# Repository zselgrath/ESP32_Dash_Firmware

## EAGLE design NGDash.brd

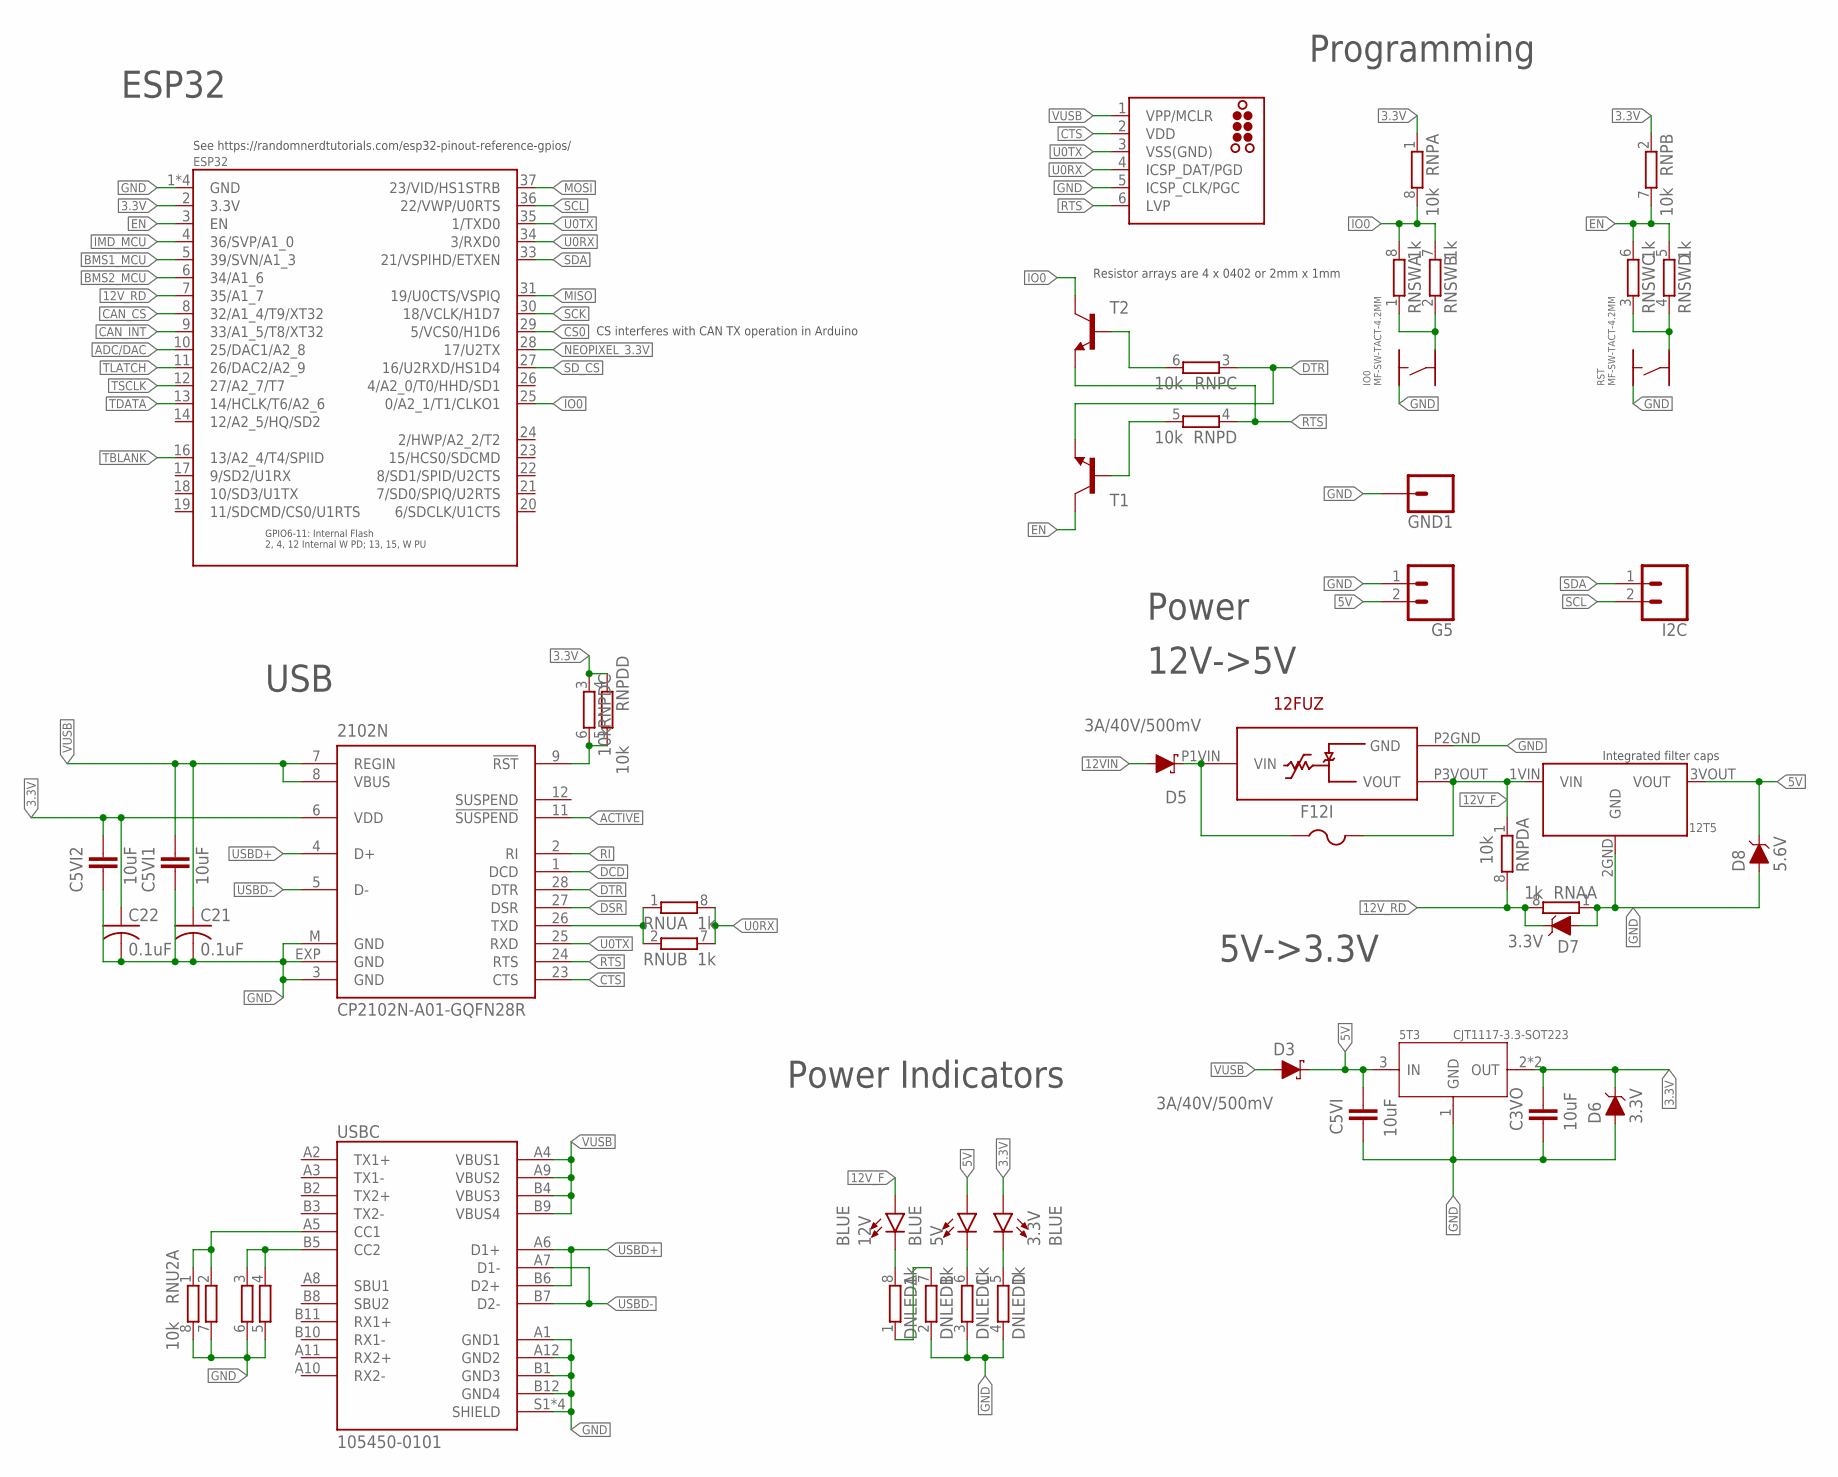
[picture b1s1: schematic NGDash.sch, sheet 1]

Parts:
3.3V, 5V, 12V: BLUE; LED-0603
5T3: CJT1117-3.3-SOT223; SOT-223
12FUZ: LITTELFUSE-POLYZEN-ZEN164V130A24LS
12T5: TRACO-TSR-2-2450
2102N: CP2102N-A01-GQFN28R; MLP28
C3VO, C5VI, C5VI1, C5VI2: 10uF; 1210
C21, C22: 0.1uF; C0603
D3, D5: 3A/40V/500mV; SMA-DIODE
D6, D7: 3.3V; SOD-323
D8: 5.6V; SOD-323
DNLED: 1k; 4X0402ARV341
ESP32: ESP32-WROOM-32; ESP32-WROOM32
F12I: PTCFUSE-1812; 1812
G5: CONN_02; 1X02
GND1: CONN_01; 1X01
I2C: CONN_02; 1X02
IO0: MF-SW-TACT-4.2MM; TACT4.2MM
J2: TC2030-MCP
RNA: 1k; 4X0402ARV341
RNP: 10k; 4X0402ARV341
RNPD: 10k; 4X0402ARV341
RNSW: 1k; 4X0402ARV341
RNU: 1k; 4X0402ARV341
RNU2: 10k; 4X0402ARV341
RST: MF-SW-TACT-4.2MM; TACT4.2MM
T1, T2: BC850-NPN-SOT23-BEC; SOT23-BEC
USBC: 105450-0101; MOLEX_105450-0101

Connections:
3.3V: 3.3V.A, 5T3.2 (OUT), 5T3.TER (OUT), 2102N.6 (VDD), C3VO.1, C5VI2.1, C22.1, D6.C, ESP32.2 (3.3V), RNP.1, RNP.2 (1), RNPD.3 (1), RNPD.4 (1); also elsewhere on the board
5V: 5T3.3 (IN), 5V.A, 12T5.3VOUT (VOUT), C5VI.1, D3.C, D8.C, G5.2; also elsewhere on the board
12VIN: D5.A; also elsewhere on the board
12VRECT: 12FUZ.P1VIN (VIN), D5.C, F12I.1
12V_F: 12FUZ.P3VOUT (VOUT), 12T5.1VIN (VIN), 12V.A, F12I.2, RNPD.1; also elsewhere on the board
12V_RD: D7.C, ESP32.7 (35/A1_7), RNA.8 (2), RNPD.8 (2)
ACTIVE: 2102N.11 (!SUSPEND)
ADC/DAC: ESP32.10 (25/DAC1/A2_8); also elsewhere on the board
BMS1_MCU: ESP32.5 (39/SVN/A1_3); also elsewhere on the board
BMS2_MCU: ESP32.6 (34/A1_6); also elsewhere on the board
CAN_CS: ESP32.8 (32/A1_4/T9/XT32); also elsewhere on the board
CAN_INT: ESP32.9 (33/A1_5/T8/XT32); also elsewhere on the board
CS0: ESP32.29 (5/VCS0/H1D6)
CTS: 2102N.23 (CTS), J2.2 (VDD)
DCD: 2102N.1 (DCD)
DSR: 2102N.27 (DSR)
DTR: 2102N.28 (DTR), RNP.3 (1), T1.E
EN: ESP32.3 (EN), RNP.7 (2), RNSW.5 (2), RNSW.6 (2), T1.C
GND: 5T3.1 (GND), 12FUZ.P2GND (GND), 12T5.2GND (GND), 2102N.3 (GND), 2102N.EXP (GND), 2102N.M (GND), C3VO.2, C5VI.2, C5VI1.2, C5VI2.2, C21.2, C22.2, D6.A, D7.A, D8.A, DNLED.2 (1), DNLED.3 (1), DNLED.4 (1), ESP32.1 (GND), ESP32.15 (GND), ESP32.38 (GND), ESP32.GND, G5.1, GND1.1, IO0.P$1, J2.5 (ICSP_CLK/PGC), RNA.1, RNU2.5 (2), RNU2.6 (2), RNU2.7 (2), RNU2.8 (2), RST.P$1, USBC.A1 (GND1), USBC.A12 (GND2), USBC.B1 (GND3), USBC.B12 (GND4), USBC.S1 (SHIELD), USBC.S2 (SHIELD), USBC.S3 (SHIELD), USBC.S4 (SHIELD); also elsewhere on the board
IMD_MCU: ESP32.4 (36/SVP/A1_0); also elsewhere on the board
IO0: ESP32.25 (0/A2_1/T1/CLKO1), RNP.8 (2), RNSW.7 (2), RNSW.8 (2), T2.C
MISO: ESP32.31 (19/U0CTS/VSPIQ); also elsewhere on the board
MOSI: ESP32.37 (23/VID/HS1STRB); also elsewhere on the board
unnamed: 5V.C, DNLED.6 (2)
unnamed: IO0.P$4, RNSW.1, RNSW.2 (1)
unnamed: RNP.5 (2), T1.B
unnamed: RNP.6 (2), T2.B
unnamed: RNU2.1, RNU2.2 (1), USBC.A5 (CC1)
unnamed: RNSW.3 (1), RNSW.4 (1), RST.P$4
unnamed: 3.3V.C, DNLED.5 (2)
unnamed: 2102N.9 (!RST), RNPD.5 (2), RNPD.6 (2)
unnamed: RNU2.3 (1), RNU2.4 (1), USBC.B5 (CC2)
unnamed: DNLED.1, DNLED.7 (2)
unnamed: 12V.C, DNLED.8 (2)
NEOPIXEL_3.3V: ESP32.28 (17/U2TX); also elsewhere on the board
RI: 2102N.2 (RI)
RTS: 2102N.24 (RTS), J2.6 (LVP), RNP.4 (1), T2.E
SCK: ESP32.30 (18/VCLK/H1D7); also elsewhere on the board
SCL: ESP32.36 (22/VWP/U0RTS), I2C.2
SDA: ESP32.33 (21/VSPIHD/ETXEN), I2C.1
SD_CS: ESP32.27 (16/U2RXD/HS1D4); also elsewhere on the board
TBLANK: ESP32.16 (13/A2_4/T4/SPIID); also elsewhere on the board
TDATA: ESP32.13 (14/HCLK/T6/A2_6); also elsewhere on the board
TLATCH: ESP32.11 (26/DAC2/A2_9); also elsewhere on the board
TSCLK: ESP32.12 (27/A2_7/T7); also elsewhere on the board
U0RX: ESP32.34 (3/RXD0), J2.4 (ICSP_DAT/PGD), RNU.7 (2), RNU.8 (2)
U0TX: 2102N.25 (RXD), ESP32.35 (1/TXD0), J2.3 (VSS(GND))
U0TXC: 2102N.26 (TXD), RNU.1, RNU.2 (1)
USBD+: 2102N.4 (D+), USBC.A6 (D1+), USBC.B6 (D2+)
USBD-: 2102N.5 (D-), USBC.A7 (D1-), USBC.B7 (D2-)
VUSB: 2102N.7 (REGIN), 2102N.8 (VBUS), C5VI1.1, C21.1, D3.A, J2.1 (VPP/MCLR), USBC.A4 (VBUS1), USBC.A9 (VBUS2), USBC.B4 (VBUS3), USBC.B9 (VBUS4)

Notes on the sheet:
Resistor arrays are 4 x 0402 or 2mm x 1mm
USB
Programming
Power
ESP32
5V->3.3V
CS interferes with CAN TX operation in Arduino
See https://randomnerdtutorials.com/esp32-pinout-reference-gpios/
12V->5V
Integrated filter caps
Power Indicators

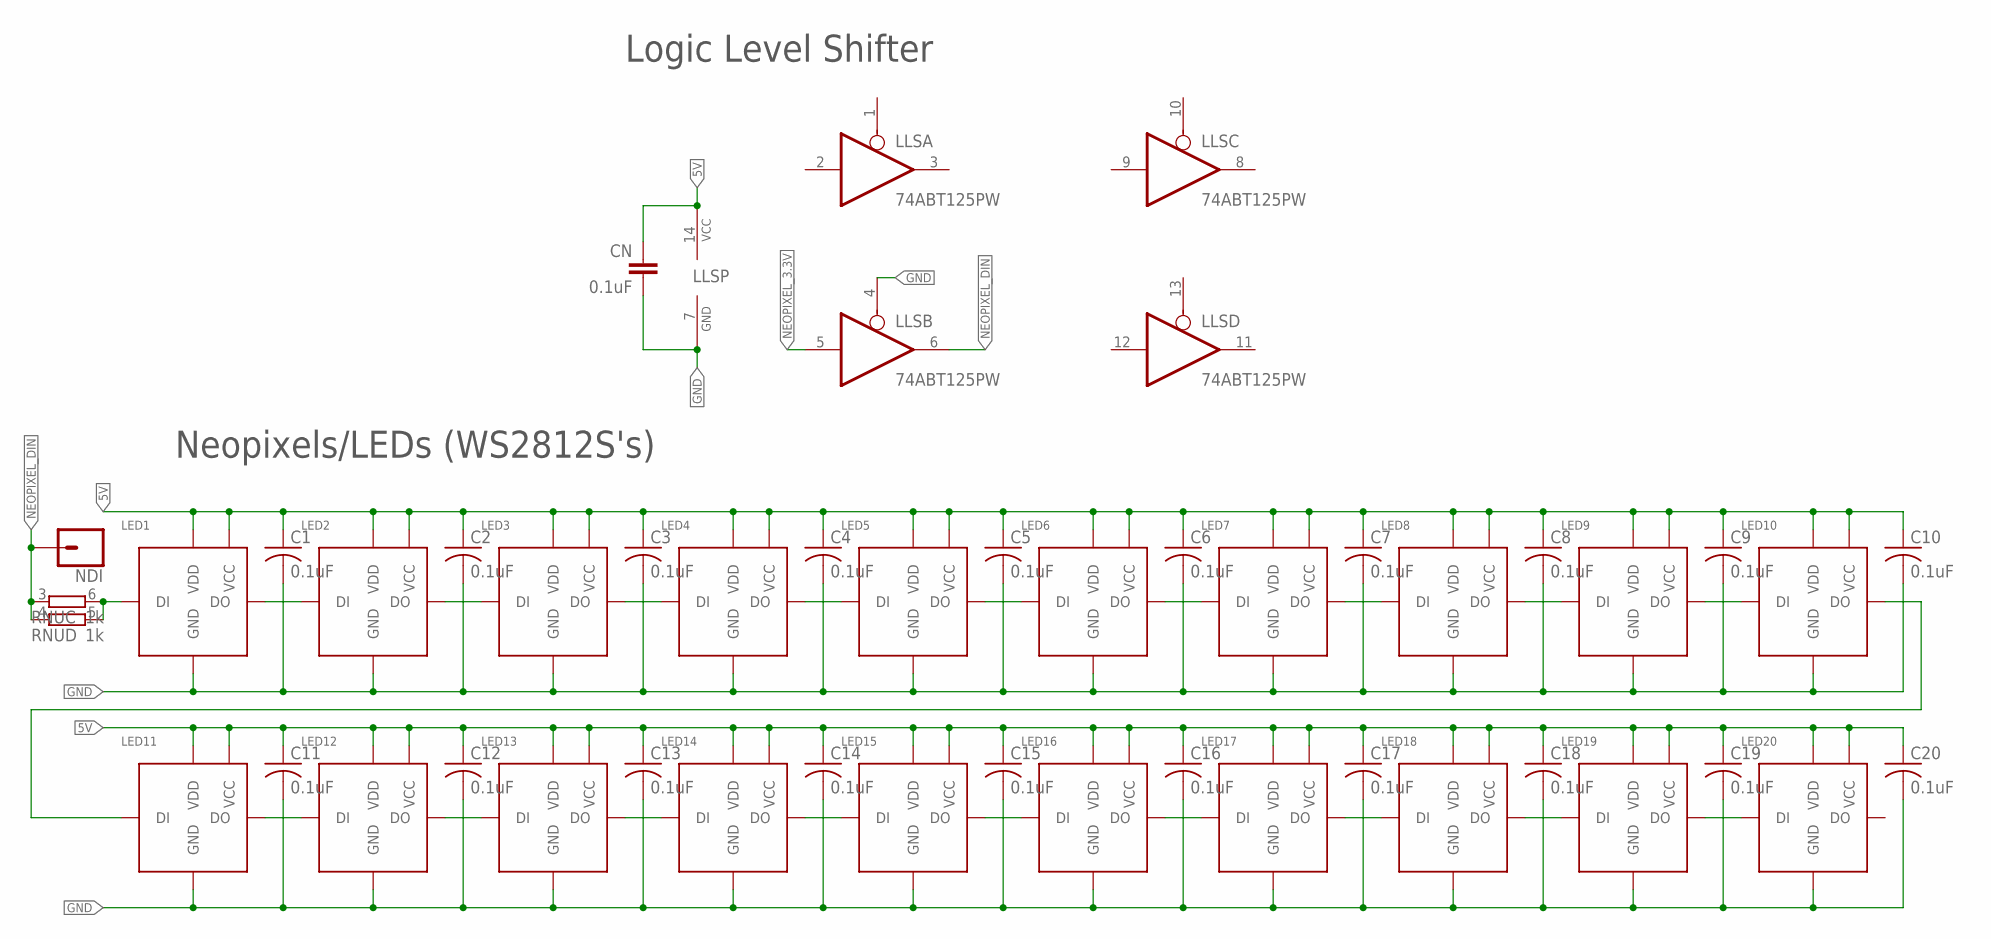
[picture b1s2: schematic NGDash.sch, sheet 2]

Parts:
C1, C2, C3, C4, C5, C6, C7, C8, C9, C10, C11, C12, C13, C14, C15, C16, C17, C18, C19, C20: 0.1uF; C0603
CN: 0.1uF; 0603-CAP
LED1, LED2, LED3, LED4, LED5, LED6, LED7, LED8, LED9, LED10, LED11, LED12, LED13, LED14, LED15, LED16, LED17, LED18, LED19, LED20: WS2812S; WS2812S5050
LLS: 74ABT125PW; TSSOP14
NDI: CONN_01; 1X01
RNU: 1k; 4X0402ARV341

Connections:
5V: C1.1, C2.1, C3.1, C4.1, C5.1, C6.1, C7.1, C8.1, C9.1, C10.1, C11.1, C12.1, C13.1, C14.1, C15.1, C16.1, C17.1, C18.1, C19.1, C20.1, CN.1, LED1.3_FS_VCC (VCC), LED1.5_FS_5V (VDD), LED2.3_FS_VCC (VCC), LED2.5_FS_5V (VDD), LED3.3_FS_VCC (VCC), LED3.5_FS_5V (VDD), LED4.3_FS_VCC (VCC), LED4.5_FS_5V (VDD), LED5.3_FS_VCC (VCC), LED5.5_FS_5V (VDD), LED6.3_FS_VCC (VCC), LED6.5_FS_5V (VDD), LED7.3_FS_VCC (VCC), LED7.5_FS_5V (VDD), LED8.3_FS_VCC (VCC), LED8.5_FS_5V (VDD), LED9.3_FS_VCC (VCC), LED9.5_FS_5V (VDD), LED10.3_FS_VCC (VCC), LED10.5_FS_5V (VDD), LED11.3_FS_VCC (VCC), LED11.5_FS_5V (VDD), LED12.3_FS_VCC (VCC), LED12.5_FS_5V (VDD), LED13.3_FS_VCC (VCC), LED13.5_FS_5V (VDD), LED14.3_FS_VCC (VCC), LED14.5_FS_5V (VDD), LED15.3_FS_VCC (VCC), LED15.5_FS_5V (VDD), LED16.3_FS_VCC (VCC), LED16.5_FS_5V (VDD), LED17.3_FS_VCC (VCC), LED17.5_FS_5V (VDD), LED18.3_FS_VCC (VCC), LED18.5_FS_5V (VDD), LED19.3_FS_VCC (VCC), LED19.5_FS_5V (VDD), LED20.3_FS_VCC (VCC), LED20.5_FS_5V (VDD), LLS.14 (VCC); also elsewhere on the board
GND: C1.2, C2.2, C3.2, C4.2, C5.2, C6.2, C7.2, C8.2, C9.2, C10.2, C11.2, C12.2, C13.2, C14.2, C15.2, C16.2, C17.2, C18.2, C19.2, C20.2, CN.2, LED1.6_FS_GND (GND), LED2.6_FS_GND (GND), LED3.6_FS_GND (GND), LED4.6_FS_GND (GND), LED5.6_FS_GND (GND), LED6.6_FS_GND (GND), LED7.6_FS_GND (GND), LED8.6_FS_GND (GND), LED9.6_FS_GND (GND), LED10.6_FS_GND (GND), LED11.6_FS_GND (GND), LED12.6_FS_GND (GND), LED13.6_FS_GND (GND), LED14.6_FS_GND (GND), LED15.6_FS_GND (GND), LED16.6_FS_GND (GND), LED17.6_FS_GND (GND), LED18.6_FS_GND (GND), LED19.6_FS_GND (GND), LED20.6_FS_GND (GND), LLS.4 (OE), LLS.7 (GND); also elsewhere on the board
unnamed: LED1.1_FS_DO (DO), LED2.2_FS_DI (DI)
unnamed: LED2.1_FS_DO (DO), LED3.2_FS_DI (DI)
unnamed: LED3.1_FS_DO (DO), LED4.2_FS_DI (DI)
unnamed: LED4.1_FS_DO (DO), LED5.2_FS_DI (DI)
unnamed: LED5.1_FS_DO (DO), LED6.2_FS_DI (DI)
unnamed: LED6.1_FS_DO (DO), LED7.2_FS_DI (DI)
unnamed: LED7.1_FS_DO (DO), LED8.2_FS_DI (DI)
unnamed: LED8.1_FS_DO (DO), LED9.2_FS_DI (DI)
unnamed: LED9.1_FS_DO (DO), LED10.2_FS_DI (DI)
unnamed: LED11.1_FS_DO (DO), LED12.2_FS_DI (DI)
unnamed: LED12.1_FS_DO (DO), LED13.2_FS_DI (DI)
unnamed: LED13.1_FS_DO (DO), LED14.2_FS_DI (DI)
unnamed: LED14.1_FS_DO (DO), LED15.2_FS_DI (DI)
unnamed: LED15.1_FS_DO (DO), LED16.2_FS_DI (DI)
unnamed: LED16.1_FS_DO (DO), LED17.2_FS_DI (DI)
unnamed: LED17.1_FS_DO (DO), LED18.2_FS_DI (DI)
unnamed: LED18.1_FS_DO (DO), LED19.2_FS_DI (DI)
unnamed: LED19.1_FS_DO (DO), LED20.2_FS_DI (DI)
unnamed: LED1.2_FS_DI (DI), RNU.5 (2), RNU.6 (2)
NDAT2: LED10.1_FS_DO (DO), LED11.2_FS_DI (DI)
NEOPIXEL_3.3V: LLS.5 (I); also elsewhere on the board
NEOPIXEL_DIN: LLS.6 (O), NDI.1, RNU.3 (1), RNU.4 (1)

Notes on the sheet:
Logic Level Shifter
Neopixels/LEDs (WS2812S's)

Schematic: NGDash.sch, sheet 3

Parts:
CSD: 0.1uF; C0603
J1: MICRO-SD_CARD_SOCKET; MICRO-SD-SOCKET
RSD, RSD1: 50k; 4X0402ARV341
_3.3V, _5V: TP
_CANH: TP
_CANL: TP
_GND: TP

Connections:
3.3V: CSD.1, J1.VCC, RSD.5 (2), RSD.6 (2), RSD.7 (2), RSD1.7 (2), RSD1.8 (2), _3.3V.P$1; also elsewhere on the board
5V: _5V.P$1; also elsewhere on the board
CANH: _CANH.P$1; also elsewhere on the board
CANL: _CANL.P$1; also elsewhere on the board
GND: CSD.2, J1.GND, J1.GND1 (SHIELD), J1.GND3 (SHIELD), RSD.8 (2), _GND.P$1; also elsewhere on the board
MISO: J1.DO, RSD.2 (1); also elsewhere on the board
MOSI: J1.DI, RSD.3 (1); also elsewhere on the board
unnamed: J1.RSV1 (RSV), RSD1.2 (1)
unnamed: J1.RSV2 (RSV), RSD1.1
SCK: J1.SCLK (SCK), RSD.1; also elsewhere on the board
SD_CS: J1.CS (!CS), RSD.4 (1); also elsewhere on the board

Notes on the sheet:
Alphanumerics
uSD Card

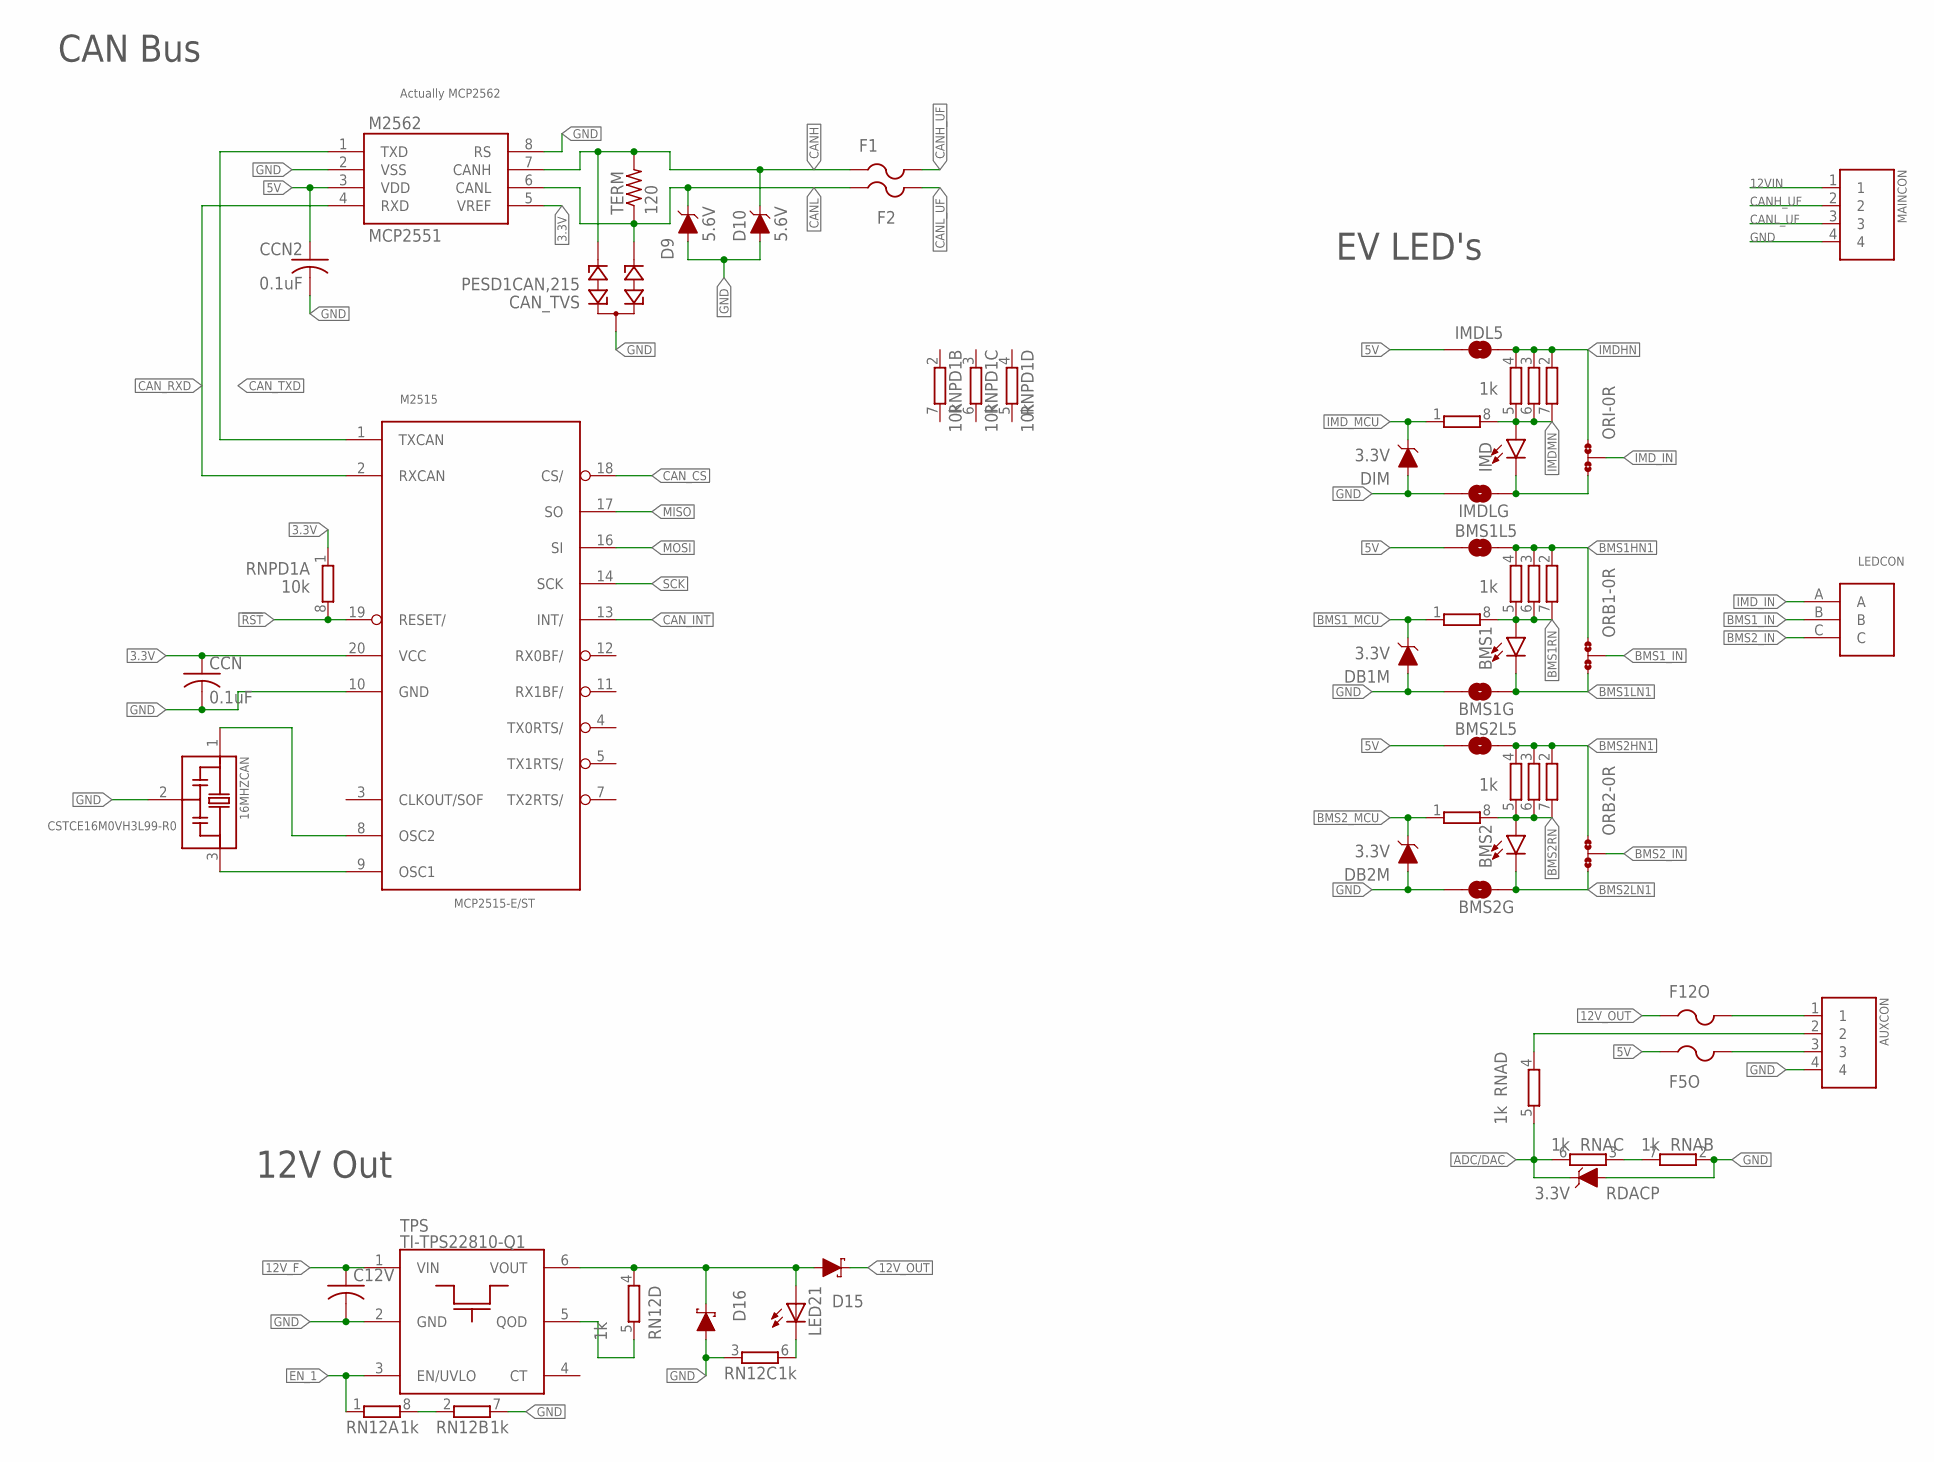
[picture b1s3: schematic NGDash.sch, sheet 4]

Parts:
16MHZCAN: CSTCE16M0VH3L99-R0; OSC_CSTCE16M0V53-R0
AUXCON: AMP-AT04-4P-BM02-DEUTSCH; AMP-AT04-4P-BM02
BMS1, BMS2: LED1206; LED-1206
BMS1G, BMS1L5, BMS2G, BMS2L5: JUMPER-SMT_2_NO_SILK; SMT-JUMPER_2_NO_SILK
C12V: C-USC0603; C0603
CAN_TVS: PESD1CAN,215; SOT23
CCN, CCN2: 0.1uF; C0603
D9, D10: 5.6V; SOD-323
D15, D16: 3A/40V/500mV; SMA-DIODE
DB1M, DB2M: 3.3V; SOD-323
DIM: 3.3V; SOD-323
F1, F2, F5O, F12O: PTCFUSE-1206; R1206
IMD: LED1206; LED-1206
IMDL5: JUMPER-SMT_2_NO_SILK; SMT-JUMPER_2_NO_SILK
IMDLG: JUMPER-SMT_2_NO_SILK; SMT-JUMPER_2_NO_SILK
LED21: LEDCHIP-LED0603; CHIP-LED0603
LEDCON: AMP-AT04-3P-BM02-DEUTSCH; AMP-AT04-3P-BM02
M2515: MCP2515-E/ST; TSSOP20
M2562: MCP2551; SO08
MAINCON: AMP-AT04-4P-BM02-DEUTSCH; AMP-AT04-4P-BM02
ORB1, ORB2: 0R-JUMPA; A0R-JMP
ORI: 0R-JUMPA; A0R-JMP
RDACP: 3.3V; SOD-323
RN12: 1k; 4X0402ARV341
RNA: 1k; 4X0402ARV341
RNB1, RNB2: 1k; 4X0402ARV341
RNI: 1k; 4X0402ARV341
RNPD1: 10k; 4X0402ARV341
TERM: 120; R0603
TPS: TI-TPS22810-Q1; SOT23-6

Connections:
3.3V: CCN.1, M2515.20 (VCC), M2562.5 (VREF), RNPD1.1; also elsewhere on the board
5V: BMS1L5.1, BMS2L5.1, CCN2.1, F5O.1, IMDL5.1, M2562.3 (VDD); also elsewhere on the board
5VOFUSED: AUXCON.3, F5O.2
12VIN: MAINCON.1; also elsewhere on the board
12VOFUSED: AUXCON.1, F12O.2
12V_F: C12V.1, TPS.1 (VIN); also elsewhere on the board
12V_OUT: D15.C, F12O.1
12V_SW: D15.A, D16.C, LED21.A, RN12.4 (1), TPS.6 (VOUT)
!RST: M2515.19 (RESET/), RNPD1.8 (2)
ADC/DAC: RDACP.C, RNA.5 (2), RNA.6 (2); also elsewhere on the board
BMS1HN1: BMS1L5.2, ORB1.1, RNB1.2 (1), RNB1.3 (1), RNB1.4 (1)
BMS1LN1: BMS1.C, BMS1G.2, ORB1.3
BMS1RN: BMS1.A, RNB1.5 (2), RNB1.6 (2), RNB1.7 (2), RNB1.8 (2)
BMS1_IN: LEDCON.B, ORB1.2
BMS1_MCU: DB1M.C, RNB1.1; also elsewhere on the board
BMS2HN1: BMS2L5.2, ORB2.1, RNB2.2 (1), RNB2.3 (1), RNB2.4 (1)
BMS2LN1: BMS2.C, BMS2G.2, ORB2.3
BMS2RN: BMS2.A, RNB2.5 (2), RNB2.6 (2), RNB2.7 (2), RNB2.8 (2)
BMS2_IN: LEDCON.C, ORB2.2
BMS2_MCU: DB2M.C, RNB2.1; also elsewhere on the board
CANH: CAN_TVS.2, D10.C, F1.1, M2562.7 (CANH), TERM.2; also elsewhere on the board
CANH_UF: F1.2, MAINCON.2
CANL: CAN_TVS.1, D9.C, F2.1, M2562.6 (CANL), TERM.1; also elsewhere on the board
CANL_UF: F2.2, MAINCON.3
CAN_CS: M2515.18 (CS/); also elsewhere on the board
CAN_INT: M2515.13 (INT/); also elsewhere on the board
CAN_RXD: M2515.2 (RXCAN), M2562.4 (RXD)
CAN_TXD: M2515.1 (TXCAN), M2562.1 (TXD)
EN_1: RN12.1, TPS.3 (EN/UVLO)
GND: 16MHZCAN.2, AUXCON.4, BMS1G.1, BMS2G.1, C12V.2, CAN_TVS.3, CCN.2, CCN2.2, D9.A, D10.A, D16.A, DB1M.A, DB2M.A, DIM.A, IMDLG.1, M2515.10 (GND), M2562.2 (VSS), M2562.8 (RS), MAINCON.4, RDACP.A, RN12.3 (1), RN12.7 (2), RNA.2 (1), TPS.2 (GND); also elsewhere on the board
IMDHN: IMDL5.2, ORI.1, RNI.2 (1), RNI.3 (1), RNI.4 (1)
IMDLN: IMD.C, IMDLG.2, ORI.3
IMDMN: IMD.A, RNI.5 (2), RNI.6 (2), RNI.7 (2), RNI.8 (2)
IMD_IN: LEDCON.A, ORI.2
IMD_MCU: DIM.C, RNI.1; also elsewhere on the board
MCU_ADC/DAC: AUXCON.2, RNA.4 (1)
MISO: M2515.17 (SO); also elsewhere on the board
MOSI: M2515.16 (SI); also elsewhere on the board
unnamed: 16MHZCAN.1, M2515.8 (OSC2)
unnamed: 16MHZCAN.3, M2515.9 (OSC1)
unnamed: LED21.C, RN12.6 (2)
unnamed: RNA.3 (1), RNA.7 (2)
unnamed: RN12.2 (1), RN12.8 (2)
QOD1: RN12.5 (2), TPS.5 (QOD)
SCK: M2515.14 (SCK); also elsewhere on the board

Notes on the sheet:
Actually MCP2562
CAN Bus
EV LED's
12V Out

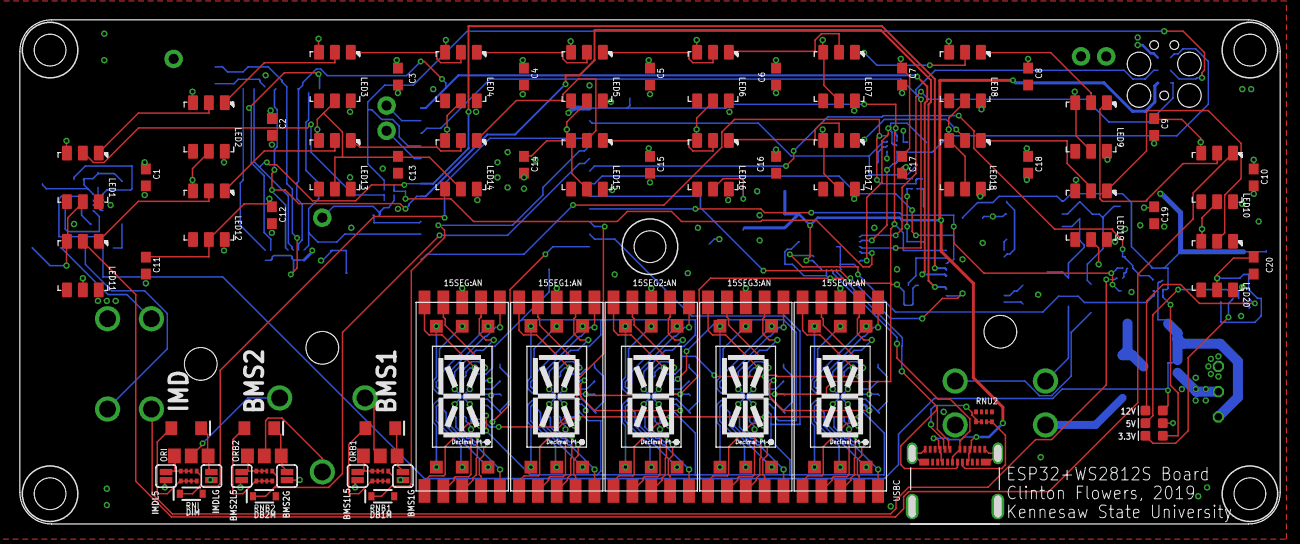
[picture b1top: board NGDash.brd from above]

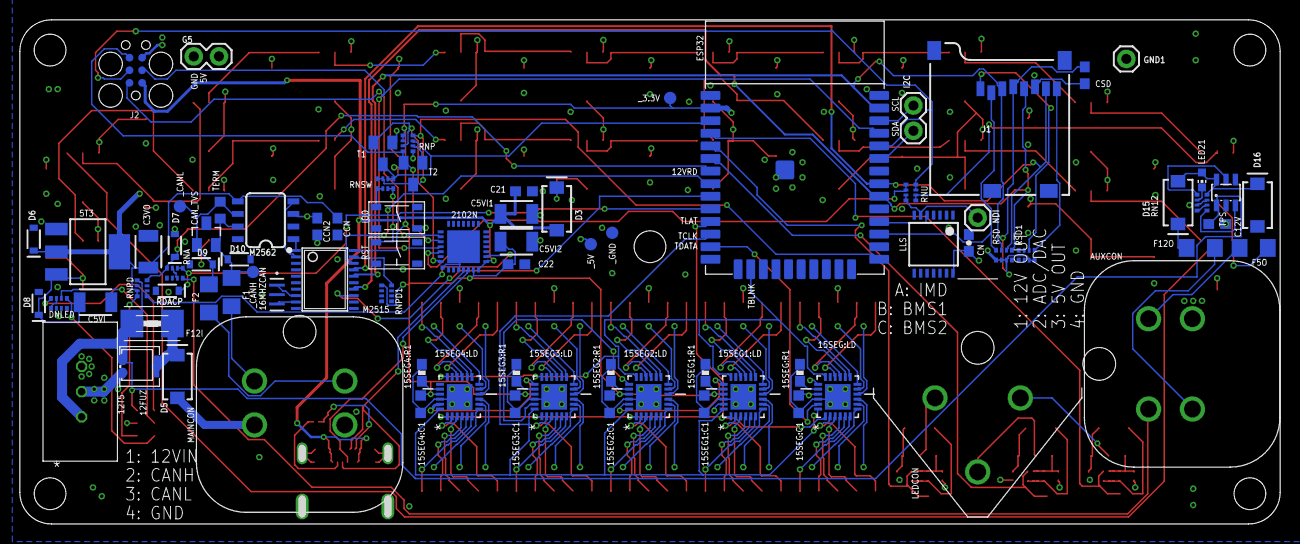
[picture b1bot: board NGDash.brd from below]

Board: 4 copper layers, 126.4 x 50.2 mm, 150 parts (82 on the bottom side), 184 nets.

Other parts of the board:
15SEG1:AN, 15SEG2:AN, 15SEG3:AN, 15SEG4:AN, 15SEG:AN: ACPSA04-41SYKWA
15SEG1:C1, 15SEG2:C1, 15SEG3:C1, 15SEG4:C1, 15SEG:C1: 0.1uF; C0603K
15SEG1:LD, 15SEG2:LD, 15SEG3:LD, 15SEG4:LD, 15SEG:LD: TLC59281RGER; QFN50P400X400X100-25N
15SEG1:R1, 15SEG2:R1, 15SEG3:R1, 15SEG4:R1, 15SEG:R1: 2.5k; 0603-RES

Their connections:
3.3V: 15SEG1:C1.1, 15SEG1:LD.21, 15SEG2:C1.1, 15SEG2:LD.21, 15SEG3:C1.1, 15SEG3:LD.21, 15SEG4:C1.1, 15SEG4:LD.21, 15SEG:C1.1, 15SEG:LD.21; also elsewhere on the board
5V: 15SEG1:AN.P$14, 15SEG2:AN.P$14, 15SEG3:AN.P$14, 15SEG4:AN.P$14, 15SEG:AN.P$14; also elsewhere on the board
15SEG1:N$1: 15SEG1:LD.20, 15SEG1:R1.1
15SEG1:N$2: 15SEG1:AN.P$1, 15SEG1:LD.2
15SEG1:N$3: 15SEG1:AN.P$2, 15SEG1:LD.3
15SEG1:N$4: 15SEG1:AN.P$3, 15SEG1:LD.4
15SEG1:N$5: 15SEG1:AN.P$4, 15SEG1:LD.5
15SEG1:N$6: 15SEG1:AN.P$5, 15SEG1:LD.6
15SEG1:N$7: 15SEG1:AN.P$6, 15SEG1:LD.7
15SEG1:N$8: 15SEG1:AN.P$7, 15SEG1:LD.8
15SEG1:N$9: 15SEG1:AN.P$8, 15SEG1:LD.9
15SEG1:N$10: 15SEG1:AN.P$9, 15SEG1:LD.10
15SEG1:N$11: 15SEG1:AN.P$10, 15SEG1:LD.11
15SEG1:N$12: 15SEG1:AN.P$11, 15SEG1:LD.12
15SEG1:N$13: 15SEG1:AN.P$12, 15SEG1:LD.13
15SEG1:N$14: 15SEG1:AN.P$13, 15SEG1:LD.14
15SEG1:N$15: 15SEG1:AN.P$15, 15SEG1:LD.15
15SEG1:N$16: 15SEG1:AN.P$16, 15SEG1:LD.16
15SEG2:N$1: 15SEG2:LD.20, 15SEG2:R1.1
15SEG2:N$2: 15SEG2:AN.P$1, 15SEG2:LD.2
15SEG2:N$3: 15SEG2:AN.P$2, 15SEG2:LD.3
15SEG2:N$4: 15SEG2:AN.P$3, 15SEG2:LD.4
15SEG2:N$5: 15SEG2:AN.P$4, 15SEG2:LD.5
15SEG2:N$6: 15SEG2:AN.P$5, 15SEG2:LD.6
15SEG2:N$7: 15SEG2:AN.P$6, 15SEG2:LD.7
15SEG2:N$8: 15SEG2:AN.P$7, 15SEG2:LD.8
15SEG2:N$9: 15SEG2:AN.P$8, 15SEG2:LD.9
15SEG2:N$10: 15SEG2:AN.P$9, 15SEG2:LD.10
15SEG2:N$11: 15SEG2:AN.P$10, 15SEG2:LD.11
15SEG2:N$12: 15SEG2:AN.P$11, 15SEG2:LD.12
15SEG2:N$13: 15SEG2:AN.P$12, 15SEG2:LD.13
15SEG2:N$14: 15SEG2:AN.P$13, 15SEG2:LD.14
15SEG2:N$15: 15SEG2:AN.P$15, 15SEG2:LD.15
15SEG2:N$16: 15SEG2:AN.P$16, 15SEG2:LD.16
15SEG3:N$1: 15SEG3:LD.20, 15SEG3:R1.1
15SEG3:N$2: 15SEG3:AN.P$1, 15SEG3:LD.2
15SEG3:N$3: 15SEG3:AN.P$2, 15SEG3:LD.3
15SEG3:N$4: 15SEG3:AN.P$3, 15SEG3:LD.4
15SEG3:N$5: 15SEG3:AN.P$4, 15SEG3:LD.5
15SEG3:N$6: 15SEG3:AN.P$5, 15SEG3:LD.6
15SEG3:N$7: 15SEG3:AN.P$6, 15SEG3:LD.7
15SEG3:N$8: 15SEG3:AN.P$7, 15SEG3:LD.8
15SEG3:N$9: 15SEG3:AN.P$8, 15SEG3:LD.9
15SEG3:N$10: 15SEG3:AN.P$9, 15SEG3:LD.10
15SEG3:N$11: 15SEG3:AN.P$10, 15SEG3:LD.11
15SEG3:N$12: 15SEG3:AN.P$11, 15SEG3:LD.12
15SEG3:N$13: 15SEG3:AN.P$12, 15SEG3:LD.13
15SEG3:N$14: 15SEG3:AN.P$13, 15SEG3:LD.14
15SEG3:N$15: 15SEG3:AN.P$15, 15SEG3:LD.15
15SEG3:N$16: 15SEG3:AN.P$16, 15SEG3:LD.16
15SEG4:N$1: 15SEG4:LD.20, 15SEG4:R1.1
15SEG4:N$2: 15SEG4:AN.P$1, 15SEG4:LD.2
15SEG4:N$3: 15SEG4:AN.P$2, 15SEG4:LD.3
15SEG4:N$4: 15SEG4:AN.P$3, 15SEG4:LD.4
15SEG4:N$5: 15SEG4:AN.P$4, 15SEG4:LD.5
15SEG4:N$6: 15SEG4:AN.P$5, 15SEG4:LD.6
15SEG4:N$7: 15SEG4:AN.P$6, 15SEG4:LD.7
15SEG4:N$8: 15SEG4:AN.P$7, 15SEG4:LD.8
15SEG4:N$9: 15SEG4:AN.P$8, 15SEG4:LD.9
15SEG4:N$10: 15SEG4:AN.P$9, 15SEG4:LD.10
15SEG4:N$11: 15SEG4:AN.P$10, 15SEG4:LD.11
15SEG4:N$12: 15SEG4:AN.P$11, 15SEG4:LD.12
15SEG4:N$13: 15SEG4:AN.P$12, 15SEG4:LD.13
15SEG4:N$14: 15SEG4:AN.P$13, 15SEG4:LD.14
15SEG4:N$15: 15SEG4:AN.P$15, 15SEG4:LD.15
15SEG4:N$16: 15SEG4:AN.P$16, 15SEG4:LD.16
15SEG:N$1: 15SEG:LD.20, 15SEG:R1.1
15SEG:N$2: 15SEG:AN.P$1, 15SEG:LD.2
15SEG:N$3: 15SEG:AN.P$2, 15SEG:LD.3
15SEG:N$4: 15SEG:AN.P$3, 15SEG:LD.4
15SEG:N$5: 15SEG:AN.P$4, 15SEG:LD.5
15SEG:N$6: 15SEG:AN.P$5, 15SEG:LD.6
15SEG:N$7: 15SEG:AN.P$6, 15SEG:LD.7
15SEG:N$8: 15SEG:AN.P$7, 15SEG:LD.8
15SEG:N$9: 15SEG:AN.P$8, 15SEG:LD.9
15SEG:N$10: 15SEG:AN.P$9, 15SEG:LD.10
15SEG:N$11: 15SEG:AN.P$10, 15SEG:LD.11
15SEG:N$12: 15SEG:AN.P$11, 15SEG:LD.12
15SEG:N$13: 15SEG:AN.P$12, 15SEG:LD.13
15SEG:N$14: 15SEG:AN.P$13, 15SEG:LD.14
15SEG:N$15: 15SEG:AN.P$15, 15SEG:LD.15
15SEG:N$16: 15SEG:AN.P$16, 15SEG:LD.16
GND: 15SEG1:C1.2, 15SEG1:LD.22, 15SEG1:LD.25, 15SEG1:R1.2, 15SEG2:C1.2, 15SEG2:LD.22, 15SEG2:LD.25, 15SEG2:R1.2, 15SEG3:C1.2, 15SEG3:LD.22, 15SEG3:LD.25, 15SEG3:R1.2, 15SEG4:C1.2, 15SEG4:LD.22, 15SEG4:LD.25, 15SEG4:R1.2, 15SEG:C1.2, 15SEG:LD.22, 15SEG:LD.25, 15SEG:R1.2; also elsewhere on the board
unnamed: 15SEG1:LD.23, 15SEG:LD.19
unnamed: 15SEG1:LD.19, 15SEG2:LD.23
unnamed: 15SEG2:LD.19, 15SEG3:LD.23
unnamed: 15SEG3:LD.19, 15SEG4:LD.23
TBLANK: 15SEG1:LD.18, 15SEG2:LD.18, 15SEG3:LD.18, 15SEG4:LD.18, 15SEG:LD.18; also elsewhere on the board
TDATA: 15SEG:LD.23; also elsewhere on the board
TLATCH: 15SEG1:LD.1, 15SEG2:LD.1, 15SEG3:LD.1, 15SEG4:LD.1, 15SEG:LD.1; also elsewhere on the board
TSCLK: 15SEG1:LD.24, 15SEG2:LD.24, 15SEG3:LD.24, 15SEG4:LD.24, 15SEG:LD.24; also elsewhere on the board

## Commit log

2019-10-20 Initial Commit
    All files received from Clinton Flowers October 19, 2019

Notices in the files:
parts and their libraries:
SparkFun-Passives: Licensing: Creative Commons ShareAlike 4.0 International - https://creativecommons.org/licenses/by-sa/4.0
tag-connect: ©2009 ROFA.cz - modified and updated by Robert Darlington ‹rdarlington@gmail.com›
